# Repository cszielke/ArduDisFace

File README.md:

# ArduDisFace
An Arduino compatible display interface with I2C, SPI and TTY/RS232 for Arduino and Raspberry PI

Layout is done in KiCad 5.0.0

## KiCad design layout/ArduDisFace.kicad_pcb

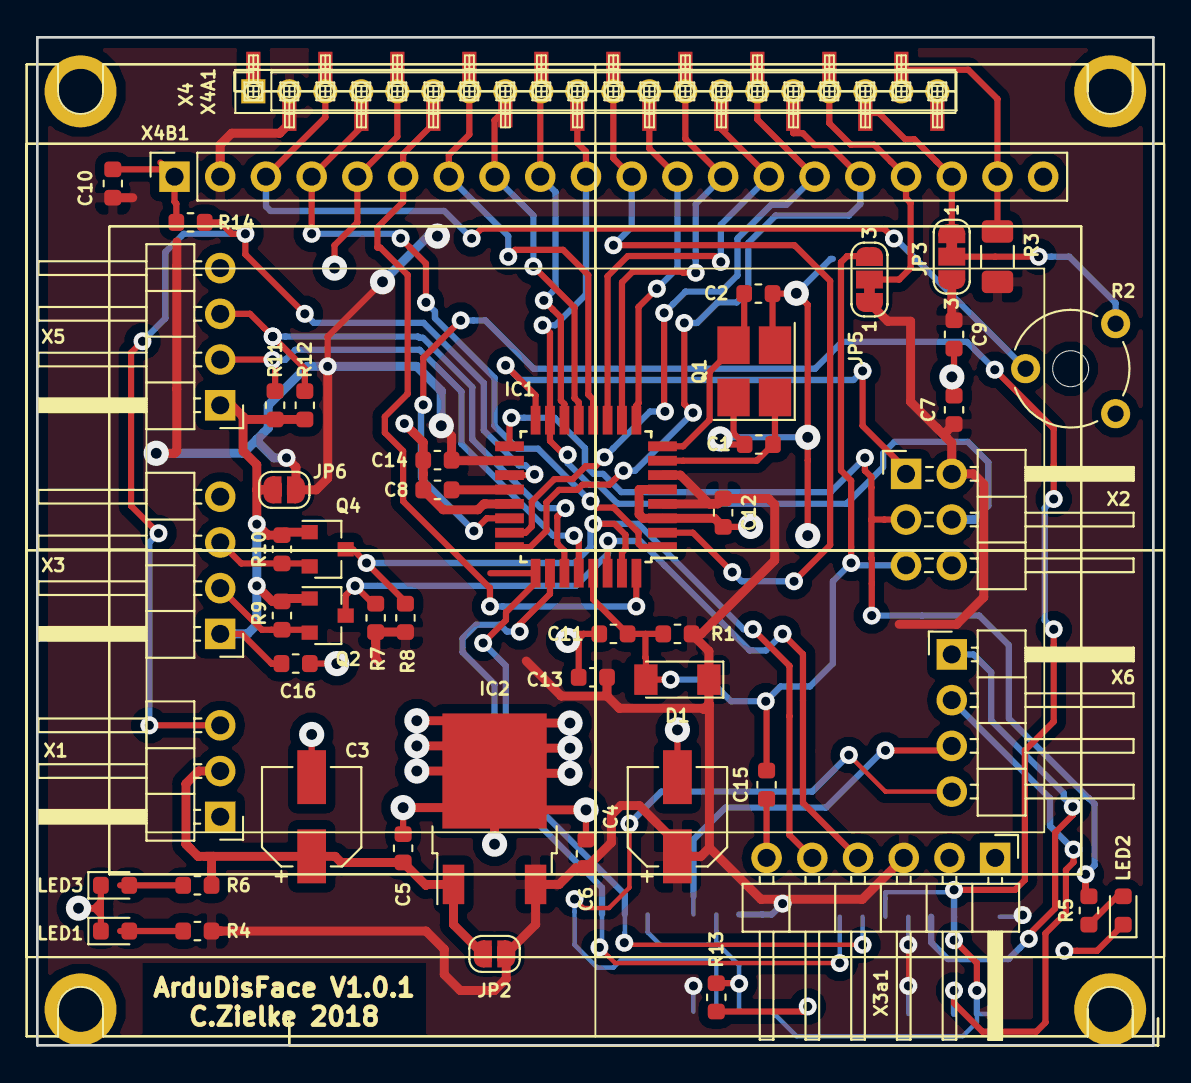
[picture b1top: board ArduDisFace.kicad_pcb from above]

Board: 2 copper layers, 62.0 x 56.0 mm, 54 parts (0 on the bottom side), 45 nets.

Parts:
C1, C2: 10p; C_0603_1608Metric
C3, C4: 10uF-35V; CP_Elec_5x5.8
C5, C6, C7, C8, C9, C10, C11, C12, C13, C14, C16: 100n; C_0603_1608Metric
C15: 1uF/10V; C_0603_1608Metric
D1: 1N4148; D_MiniMELF
IC1: ATmega328P-AU; TQFP-32_7x7mm_P0.8mm
IC2: LP2950-5.0_TO252; TO-252-2
JP2: Vin=5V; SolderJumper-2_P1.3mm_Open_RoundedPad1.0x1.5mm
JP3: VEE-VCC; SolderJumper-3_P1.3mm_Bridged12_RoundedPad1.0x1.5mm_NumberL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
JP5: G-RES; SolderJumper-3_P1.3mm_Bridged12_RoundedPad1.0x1.5mm_NumberL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
JP6: 5V; SolderJumper-2_P1.3mm_Open_RoundedPad1.0x1.5mm
LED1: 5V; D_0603_1608Metric
LED2: D13; D_0603_1608Metric
LED3: Vin; D_0603_1608Metric
Q1: 16MHz; Crystal_SMD_3225-4Pin_3.2x2.5mm_HandSoldering
Q2, Q4: BSS138; SOT-23
R1: 10K; R_0603_1608Metric
R2: 47K; Potentiometer_Piher_PT-6-V_Vertical_Hole
R3: 47; R_1206_3216Metric
R4: 470; R_0603_1608Metric
R5: 1K2; R_0603_1608Metric
R6: 2K2; R_0603_1608Metric
R7, R8, R9, R10, R11, R12: 4K7; R_0603_1608Metric
R13, R14: 100K; R_0603_1608Metric
U1, U2: 4052; SOIC-16_3.9x9.9mm_P1.27mm
X1: Power; PinHeader_1x03_P2.54mm_Horizontal
X2: ISCP; PinHeader_2x03_P2.54mm_Horizontal
X3: RS232-RPI; PinHeader_1x04_P2.54mm_Horizontal
X3a1: Prog; PinHeader_1x06_P2.54mm_Horizontal
X4: LCD; MG12064E
X4A1: LCD-A; PinSocket_1x20_P2.00mm_Vertical
X4B1: LCD-B; PinSocket_1x20_P2.54mm_Vertical
X5: I2C; PinHeader_1x04_P2.54mm_Horizontal
X6: Touch; PinHeader_1x04_P2.54mm_Horizontal

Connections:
+3V3: C16.1, JP6.2, Q2.1, Q4.1, R9.1, R10.1, R11.1, R12.1, X3.1, X5.1
+12V: C3.1, C5.1, IC2.1, JP2.1, R6.1, X1.2
/A0: IC1.23, X4.15, X4A1.15, X4B1.15
/A1: IC1.24, X4.16, X4A1.16, X4B1.16
/A2: IC1.25, U1.10, U2.10
/A3: IC1.26, U1.9, U2.9
/A4: IC1.27, R12.2, X5.3
/A5: IC1.28, R11.2, X5.2
/A6: IC1.19, R14.1, X1.3
/A7: IC1.22, R13.1, U1.1, U1.2, U1.11, U1.14, U2.1, U2.2, U2.11, U2.14
/AREF: C8.2, IC1.20
/D0: IC1.30, Q2.3, R7.2, X3a1.4
/D1: IC1.31, Q4.3, R8.2, X3a1.5
/D2: IC1.32, X4.6, X4A1.6, X4B1.6
/D3: IC1.1, X4.4, X4A1.4, X4B1.4
/D4: IC1.2, X4.11, X4A1.11, X4B1.11
/D5: IC1.9, X4.12, X4A1.12, X4B1.12
/D6: IC1.10, X4.13, X4A1.13, X4B1.13
/D7: IC1.11, X4.14, X4A1.14, X4B1.14
/D8: IC1.12, X4.7, X4A1.7, X4B1.7
/D9: IC1.13, X4.8, X4A1.8, X4B1.8
/D10: IC1.14, X4.9, X4A1.9, X4B1.9
/D11: IC1.15, X2.4, X4.10, X4A1.10, X4B1.10
/D12: IC1.16, X2.1
/D13: IC1.17, R5.1, X2.3
/DTR: C15.1, X3a1.6
/RESET: C11.2, C15.2, D1.2, IC1.29, JP5.3, R1.2, X2.5
/VEE: JP3.1, X4.18, X4A1.18, X4B1.18
/VO: R2.2, X4.3, X4A1.3, X4B1.3
/XTAL1: C1.1, IC1.7, Q1.1
/XTAL2: C2.2, IC1.8, Q1.3
GND: C1.2, C2.1, C3.2, C4.2, C5.2, C6.2, C7.2, C8.1, C9.2, C10.1, C11.1, C12.2, C13.2, C14.2, C16.2, IC1.3, IC1.5, IC1.21, IC2.2, LED1.1, LED2.1, LED3.1, Q1.2, Q1.4, R2.3, R13.2, R14.2, U1.5, U1.6, U1.7, U1.8, U1.12, U2.4, U2.6, U2.7, U2.8, U2.15, X1.1, X2.6, X3.4, X3a1.1, X3a1.2, X4.1, X4.5, X4.20, X4A1.1, X4A1.5, X4A1.20, X4B1.1, X4B1.5, X4B1.20, X5.4
unnamed: JP3.2, R2.1
unnamed: JP5.2, X4.17, X4A1.17, X4B1.17
unnamed: LED1.2, R4.2
unnamed: LED2.2, R5.2
unnamed: LED3.2, R6.2
unnamed: Q2.2, R9.2, X3.2
unnamed: Q4.2, R10.2, X3.3
unnamed: R3.2, X4.19, X4A1.19, X4B1.19
unnamed: U1.3, X6.4
unnamed: U1.13, X6.3
unnamed: U2.3, X6.2
unnamed: U2.13, X6.1
VCC: C4.1, C6.1, C7.1, C9.1, C10.2, C12.1, C13.1, C14.1, D1.1, IC1.4, IC1.6, IC1.18, IC2.3, JP2.2, JP3.3, JP5.1, JP6.1, R1.1, R3.1, R4.1, R7.1, R8.1, U1.4, U1.15, U1.16, U2.5, U2.12, U2.16, X2.2, X3a1.3, X4.2, X4A1.2, X4B1.2

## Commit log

2018-11-19 Initial check in
2018-11-19 Readme.md changed
2018-11-19 Typo...
2018-11-19 Added scheet in README.md
2018-11-19 How to connect touch or keys
2018-11-19 Adding datasheets
2018-11-19 Added test program
2018-12-04 Touch interface with only one ADC input. Usin D3 for direction input
2019-03-01 Datasheet MCP23x17.pdf
